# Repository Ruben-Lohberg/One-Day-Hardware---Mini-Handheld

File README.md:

# One-Day Hardware: Mini Handheld

**My goal was to design a handheld with a display and buttons in one day, including the PCB, enclosure, and firmware.**

I settled on a little handheld that plays Snake. By the end of the day, I'd routed the board, designed the case, and run the firmware in an emulator. I'd also ordered assembled boards from JLCPCB and parts from other vendors, and started printing the case and a PCB fit model.

## Tools

- KiCad 10.0 with the [JLCPCB Tools plugin](https://github.com/Bouni/kicad-jlcpcb-tools)
- FreeCAD 1.1.3
- Bambu Lab A1 3D printer and Bambu Studio
- Codex GPT-6.1 sol

## Try it while the boards are in the mail

**[Play Snake in your browser](https://ruben-lohberg.github.io/One-Day-Hardware---Mini-Handheld/)**. Press an arrow key or tap the on-screen D-pad to start. The demo runs the same Snake code compiled to WebAssembly and models how the TFT receives pixels over SPI.

Renode is an emulator that runs the compiled STM32 firmware on a virtual version of the handheld, with simulated buttons and a display.

To try it, run this from the repo on Windows with Python 3, LLVM, and Renode installed.

```powershell
.\firmware\run-web.ps1
```

Open [localhost:8765](http://127.0.0.1:8765/). The browser sends button presses to Renode and shows the pixels written by the STM32 firmware. The [firmware guide](firmware/README.md) has the commands for running the timing mock locally and testing the firmware.

## 1. Major component decisions

I knew I wanted JLCPCB to assemble the boards so I wouldn't have to solder all the small parts by hand. I compared microcontroller prices on JLCPCB and display prices on LCSC to find an affordable pair with enough memory for the game and a screen I could drive over SPI. Codex GPT-6.1 sol helped me compare the parts and check the pinouts and flex drawings.

- **STM32G070CBT6.** This is a 48-pin Arm Cortex-M0+ with up to 64 MHz clock speed, 128 KB of flash and 36 KB of RAM. It had enough memory for Snake and enough pins for the buttons, LEDs, SPI display and SWD. JLCPCB could fit it as part of the assembly order. [ST specifications](https://www.st.com/en/microcontrollers-microprocessors/stm32g070cb.html) · [JLCPCB C529338](https://jlcpcb.com/partdetail/STM32G070CBT6/C529338)
- **HS20HS072RX.** This is a 240 × 320 color TFT with a roughly 2-inch diagonal, an ST7789-family controller, a four-wire SPI interface and a 12-pin flex. It was small enough for the handheld and let me send pixel updates straight to the display without keeping a full screen buffer in the STM32's RAM. I could order the display separately and have JLCPCB fit the flex socket. [LCSC C5329582](https://www.lcsc.com/product-detail/C5329582.html) · [Display datasheet](https://datasheet.lcsc.com/datasheet/pdf/75d064ee0eeae326e605dda9d4b98e7e.pdf?productCode=C5329582)

## 2. KiCad schematic

I used USB-C for 5 V power and left the USB data lines unused. I brought out target voltage sense, ground, SWDIO, SWCLK, and reset to a five-pin header for the J-Link. With the STM32G070, four switches with pull-ups, and two red LEDs, I had something simple to test before asking the screen to do anything.

I used SPI for pixels, a GPIO for data/command and a PWM output for the backlight. I changed the logic rail from 3.3 V to 3.0 V to give the display supply more headroom and left the backlight on the USB rail. Codex GPT-6.1 sol helped cross-check the symbol pins and footprints against the drawings and run KiCad's electrical rule check.

Open the [KiCad project](mini_handheld/mini_handheld.kicad_pro) to see the schematic and board. The [assembly notes](manufacturing/jlcpcb/#swd-header) show how to wire the J-Link.

## 3. KiCad board

I chose surface-mount parts wherever I could and kept them on one side so JLCPCB could populate them in a single SMT assembly pass. That kept assembly costs down and left me two connectors to solder by hand. The right-angle SWD header is the through-hole exception, and the USB-C receptacle has surface-mount contacts and through-hole shell anchors.

My first outline was 60 × 95 mm. The display didn't need a board behind all of it, so I let the case carry the glass. That took the PCB down to **42 × 56 mm**. The display flex folds back under the panel into a bottom-contact socket. USB comes out on the left, SWD on the right, and the buttons stay in a cross below the display.

Both views use the same orientation so I can follow a trace through a via from one layer to the other. I hid the ground pours and silkscreen here to make the traces easier to follow.

On this board, the shortest trace wasn't always the one I wanted. I kept the display clock short while routing more of it over ground on the opposite layer. I also increased the spacing between the long SWD traces. Codex GPT-6.1 sol helped compare route lengths and ground coverage. KiCad found **zero ERC violations, zero board DRC violations, and zero unrouted connections**. The schematic parity check flagged the four mounting holes, which exist only on the PCB.

## 4. Electrical simulations

I wanted to see what the rail would do if USB sagged at the same time the load stepped up. With the USB source at 4.4 V and a simulated 25 → 75 mA load step, the 3.0 V rail dropped to **2.979 V** in the nominal case and **2.929 V** in the stress case. The deeper dip farther right is a separate input fault I added on purpose.

Codex GPT-6.1 sol helped write the SPICE decks and compare display clock edges using ST's IBIS output models. I chose medium GPIO slew and 2 MHz SPI for the first firmware. I'll measure the rail voltage and SPI clock with the real screen connected. See the [simulation files and commands](sim/README.md).

## 5. Emulation and firmware development

I started with the four buttons and two LEDs, then added a display diagnostic before moving on to Snake. Renode runs the compiled Cortex-M0+ firmware, and the virtual display turns its SPI writes into RGB565 pixels. The on-screen D-pad drives the same active-low GPIO inputs as the physical switches.

I added an animated rainbow border to show the display's color range and make refresh speed easier to see. The firmware cycles through RGB565 colors and aims to redraw the border about 30 times a second over the 2 MHz SPI link.

Codex GPT-6.1 sol helped with the STM32 code, Renode's SPI and display models, and the test scripts. The tests cover the buttons and LEDs, display updates, steering, growth, scoring, wall collisions and retry. I also checked that the model catches an early chip-select release and a missing PB15 setup bit. The [firmware notes](firmware/README.md) show how to run the checks.

## 6. FreeCAD enclosure

I exported the PCB from KiCad as a STEP file to check the fit in FreeCAD. The case supports the display on ledges and holds the PCB on four standoffs. I needed the flex to reach the socket without getting pinched by the lid.

Here's the full board with the display in place. The inset shows how the orange flex folds back under the panel and enters the Hirose socket. I made the socket translucent in FreeCAD so you can see where the end of the flex sits.

The case measures **47.2 × 95.2 × 15.0 mm**, excluding the buttons. It has a tray, a bezel, and four individual plungers. A lip on each plunger keeps it in the bezel while the case is closed. Codex GPT-6.1 sol helped me script the geometry and check the clearances with the buttons released and pressed.

The [FreeCAD model](mechanical/enclosure/enclosure.FCStd), [assembly notes and STLs](mechanical/enclosure/README.md) and [STEP export workflow](mechanical/README.md) are in the repo.

## 7. Order board and parts

I ordered five boards from JLCPCB with the surface-mount parts and flex socket fitted. I'll solder the USB-C receptacle and SWD header myself, then plug in the separately ordered display. Codex GPT-6.1 sol helped compare assembly costs and check the placement file. The [manufacturing folder](manufacturing/jlcpcb/) has the upload files and a short parts list.

## 8. 3D print prototype

I started printing the enclosure and a PCB fit model while waiting for the parts. The fit model gives me the board outline, mounting holes and connector envelopes so I can check the tray and ports without risking a real board.

This is the saved slicer preview of the fit-print arrangement. Use the [current STLs](mechanical/enclosure/README.md) when preparing a new print.

I printed the tray, bezel, four button plungers, and stand-ins for the PCB and screen.

I dropped the printed PCB and screen into the tray. With the bezel beside it, I can see where the board sits and how the screen lines up with the window.

Here it is with the bezel on and all four buttons in place. From the side you can see where the connector opening lands.

Once the parts are here, I'll add photos of the delivered boards and first assembly. On the bench I'll check for shorts, measure the 3.0 V rail, connect J-Link and run the button/LED and screen diagnostics before trying Snake. I still need to check the flex latch, USB plug clearance and switch travel on real parts.

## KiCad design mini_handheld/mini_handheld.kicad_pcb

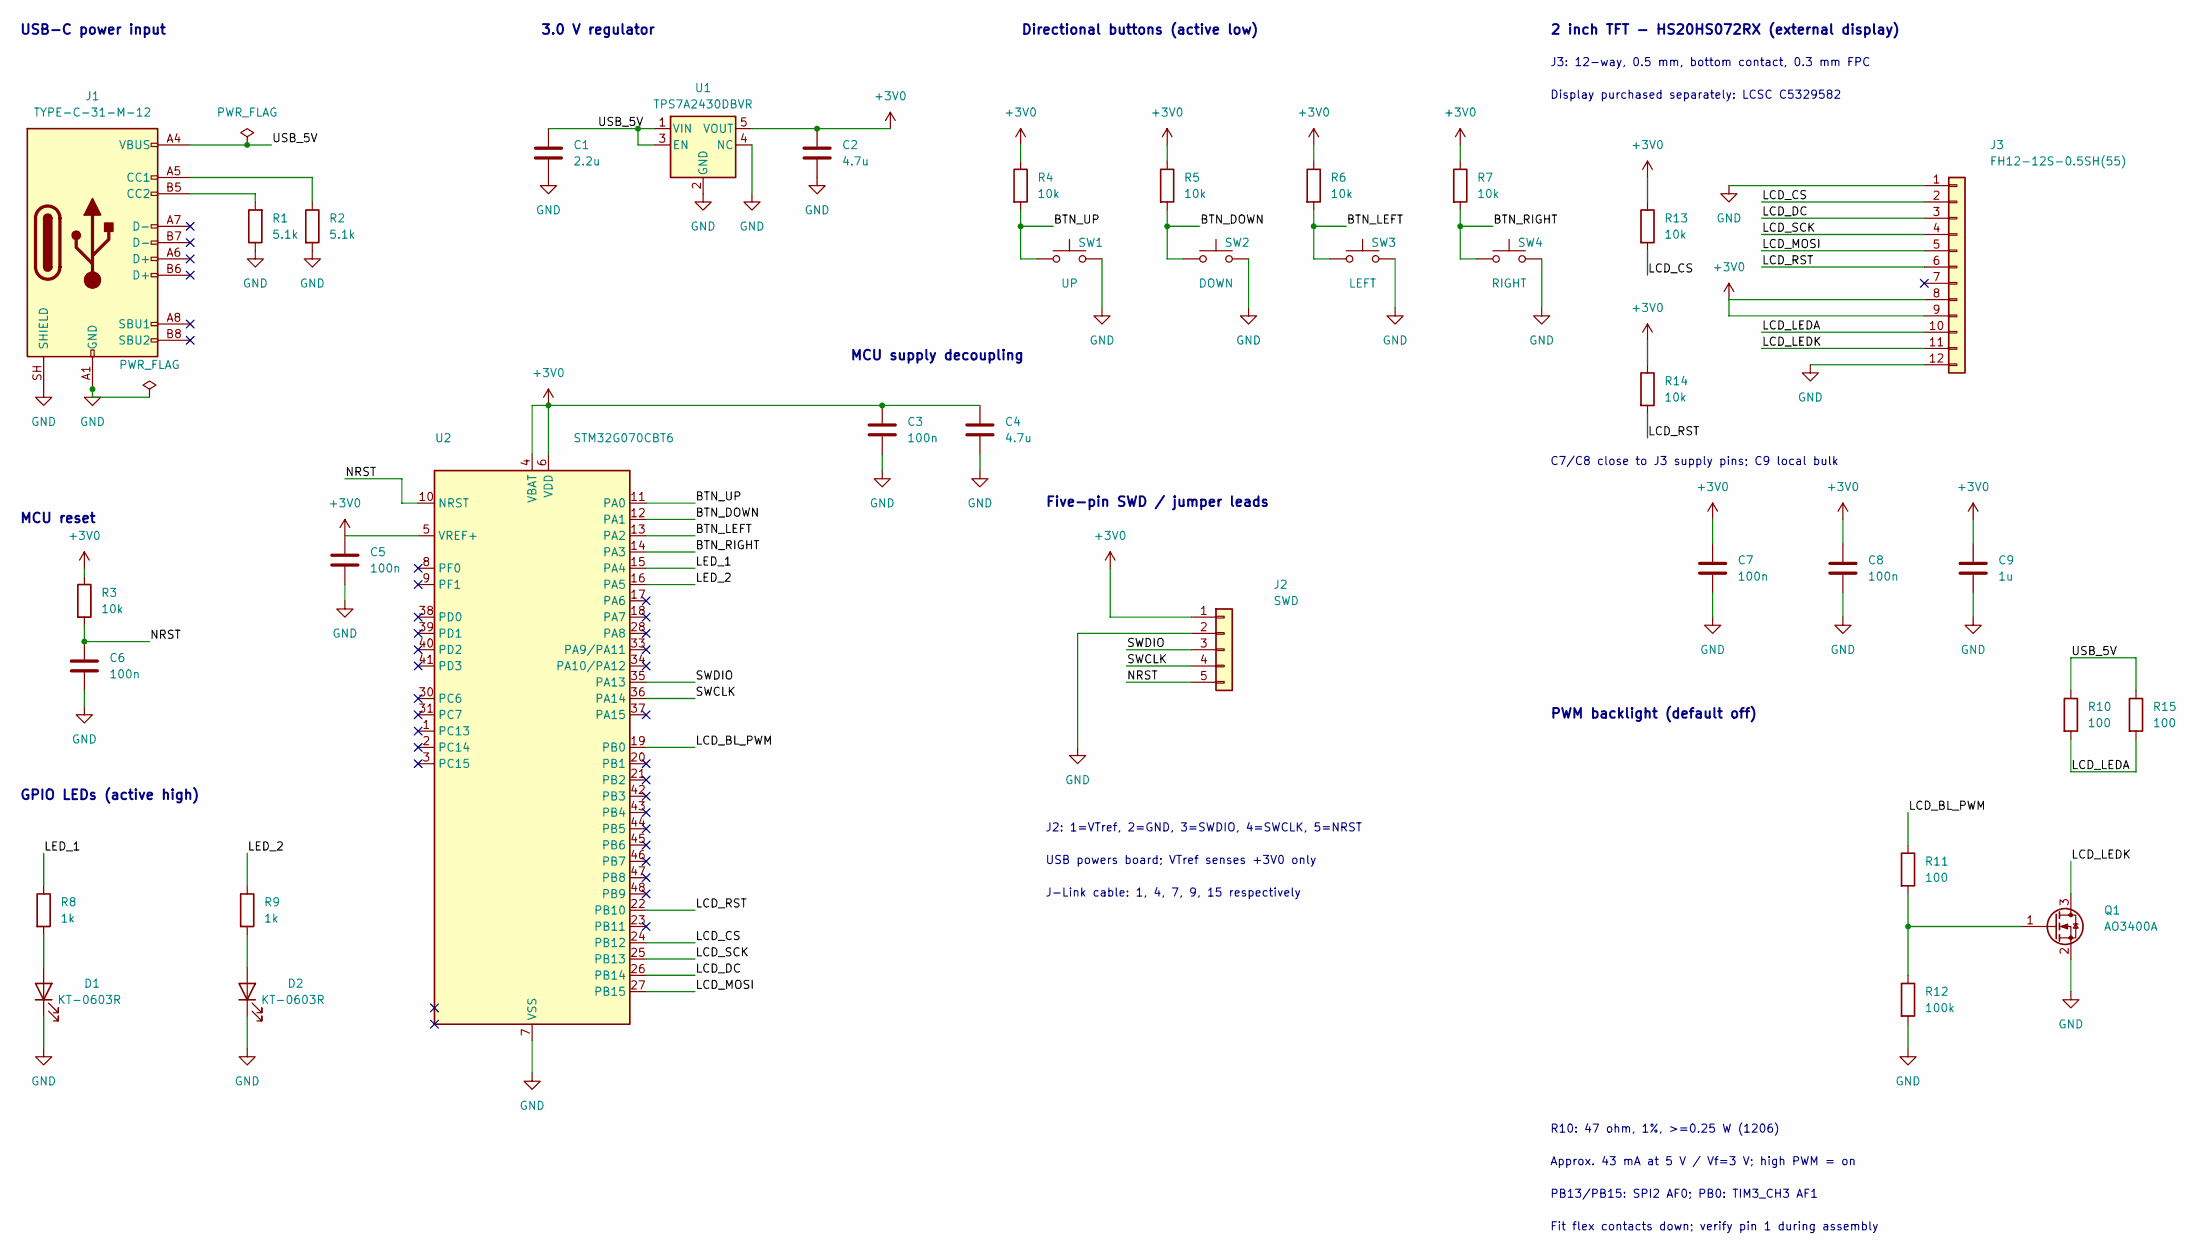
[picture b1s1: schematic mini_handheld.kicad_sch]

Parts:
C1: 2.2u; C_0603_1608Metric; Tolerance 10%; Voltage 50V; MPN CL10A225KO8NNNC; LCSC C23630
C2, C4: 4.7u; C_0805_2012Metric; Tolerance 10%; Voltage 25V; MPN CL21A475KAQNNNE; LCSC C1779
C3, C5, C6, C7, C8: 100n; C_0603_1608Metric; Tolerance 10%; Voltage 50V; MPN CC0603KRX7R9BB104; LCSC C14663
C9: 1u; C_0603_1608Metric; Tolerance 10%; Voltage 50V; MPN CL10A105KB8NNNC; LCSC C15849
D1, D2: KT-0603R; LED_0603_1608Metric; MPN KT-0603R; LCSC C2286
J1: TYPE-C-31-M-12; USB_C_Receptacle_HRO_TYPE-C-31-M-12_Edge; MPN TYPE-C-31-M-12; LCSC C165948
J2: SWD; PinHeader_1x05_P2.54mm_Horizontal_Edge
J3: FH12-12S-0.5SH(55); Hirose_FH12-12S-0.5SH_1x12-1MP_P0.50mm_Horizontal; MPN FH12-12S-0.5SH(55); LCSC C88360
Q1: AO3400A; SOT-23; MPN AO3400A; LCSC C20917
R1, R2: 5.1k; R_0603_1608Metric; Tolerance 1%; Voltage 75V; MPN 0603WAF5101T5E; LCSC C23186
R3, R4, R5, R6, R7, R13, R14: 10k; R_0603_1608Metric; Tolerance 1%; Voltage 75V; MPN 0603WAF1002T5E; LCSC C25804
R8, R9: 1k; R_0603_1608Metric; Tolerance 1%; Voltage 75V; MPN 0603WAF1001T5E; LCSC C21190
R10, R11, R15: 100; R_0603_1608Metric; Tolerance 1%; Voltage 75V; MPN 0603WAF1000T5E; LCSC C22775
R12: 100k; R_0603_1608Metric; Tolerance 1%; Voltage 75V; MPN 0603WAF1003T5E; LCSC C25803
SW1: UP; SW_SPST_TS-1088-xR020; MPN TS-1088-AR02016; LCSC C720477
SW2: DOWN; SW_SPST_TS-1088-xR020; MPN TS-1088-AR02016; LCSC C720477
SW3: LEFT; SW_SPST_TS-1088-xR020; MPN TS-1088-AR02016; LCSC C720477
SW4: RIGHT; SW_SPST_TS-1088-xR020; MPN TS-1088-AR02016; LCSC C720477
U1: TPS7A2430DBVR; SOT-23-5; MPN TPS7A2430DBVR; LCSC C2864435
U2: STM32G070CBT6; LQFP-48_7x7mm_P0.5mm; MPN STM32G070CBT6; LCSC C529338

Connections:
+3V0: C2.1, C3.1, C4.1, C5.1, C7.1, C8.1, C9.1, J2.1, J3.8, J3.9, R3.1, R4.1, R5.1, R6.1, R7.1, R13.1, R14.1, U1.5 (VOUT), U2.4 (VBAT), U2.5 (VREF+), U2.6 (VDD)
/BTN_DOWN: R5.2, SW2.1, U2.12 (PA1)
/BTN_LEFT: R6.2, SW3.1, U2.13 (PA2)
/BTN_RIGHT: R7.2, SW4.1, U2.14 (PA3)
/BTN_UP: R4.2, SW1.1, U2.11 (PA0)
/LCD_BL_PWM: R11.1, U2.19 (PB0)
/LCD_CS: J3.2, R13.2, U2.24 (PB12)
/LCD_DC: J3.3, U2.26 (PB14)
/LCD_LEDA: J3.10, R10.2, R15.2
/LCD_LEDK: J3.11, Q1.3 (D)
/LCD_MOSI: J3.5, U2.27 (PB15)
/LCD_RST: J3.6, R14.2, U2.22 (PB10)
/LCD_SCK: J3.4, U2.25 (PB13)
/LED_1: R8.1, U2.15 (PA4)
/LED_2: R9.1, U2.16 (PA5)
/NRST: C6.1, J2.5, R3.2, U2.10 (NRST)
/SWCLK: J2.4, U2.36 (PA14)
/SWDIO: J2.3, U2.35 (PA13)
/USB_5V: C1.1, J1.A4 (VBUS), J1.A9 (VBUS), J1.B4 (VBUS), J1.B9 (VBUS), R10.1, R15.1, U1.1 (VIN), U1.3 (EN)
GND: C1.2, C2.2, C3.2, C4.2, C5.2, C6.2, C7.2, C8.2, C9.2, D1.1 (K), D2.1 (K), J1.A1 (GND), J1.A12 (GND), J1.B1 (GND), J1.B12 (GND), J1.SH (SHIELD), J2.2, J3.1, J3.12, Q1.2 (S), R1.1, R2.2, R12.2, SW1.2, SW2.2, SW3.2, SW4.2, U1.2 (GND), U1.4 (NC), U2.7 (VSS)
unnamed: D1.2 (A), R8.2
unnamed: D2.2 (A), R9.2
unnamed: J1.A5 (CC1), R2.1
unnamed: J1.B5 (CC2), R1.2
unnamed: Q1.1 (G), R11.2, R12.1

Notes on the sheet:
3.0 V regulator
Fit flex contacts down; verify pin 1 during assembly
GPIO LEDs (active high)
J2: 1=VTref, 2=GND, 3=SWDIO, 4=SWCLK, 5=NRST
Display purchased separately: LCSC C5329582
PWM backlight (default off)
MCU reset
MCU supply decoupling
J-Link cable: 1, 4, 7, 9, 15 respectively
Approx. 43 mA at 5 V / Vf=3 V; high PWM = on
PB13/PB15: SPI2 AF0; PB0: TIM3_CH3 AF1
Five-pin SWD / jumper leads
J3: 12-way, 0.5 mm, bottom contact, 0.3 mm FPC
USB-C power input
2 inch TFT - HS20HS072RX (external display)
Directional buttons (active low)
C7/C8 close to J3 supply pins; C9 local bulk
R10: 47 ohm, 1%, >=0.25 W (1206)
USB powers board; VTref senses +3V0 only

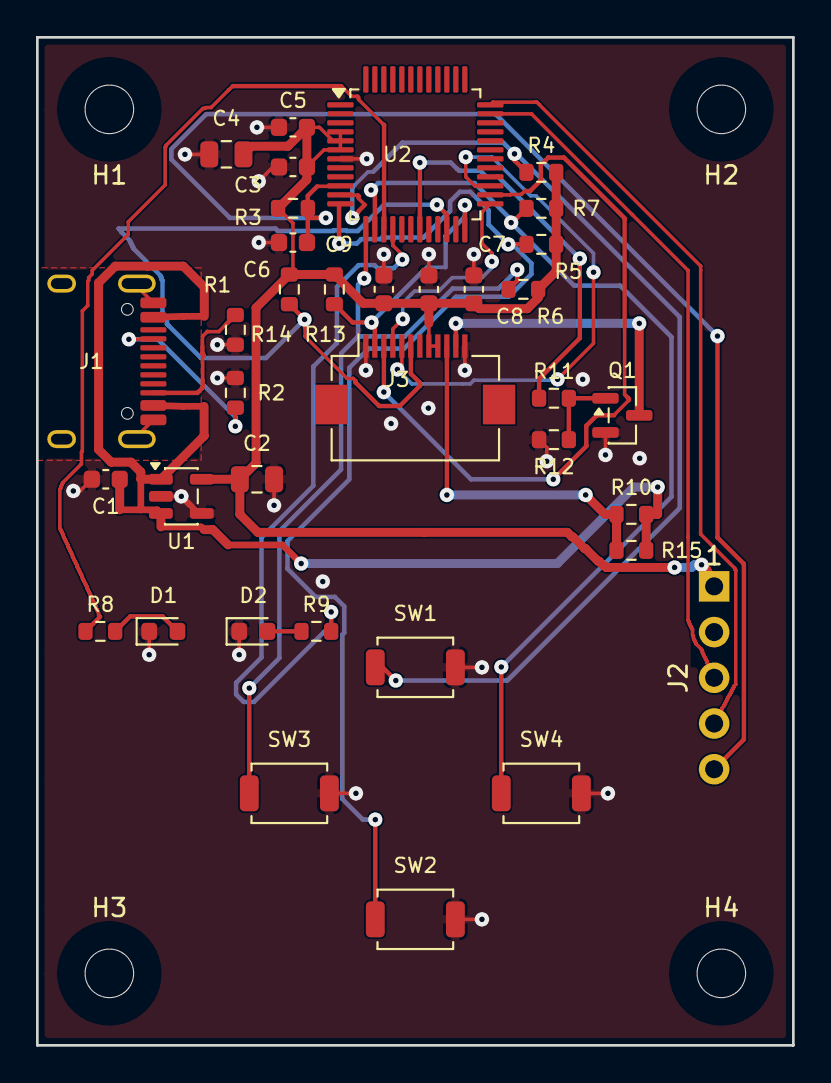
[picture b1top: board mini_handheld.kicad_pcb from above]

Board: 2 copper layers, 42.0 x 56.0 mm, 40 parts (0 on the bottom side), 25 nets.

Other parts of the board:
H1, H2, H3, H4: MountingHole_2.7mm_M2.5

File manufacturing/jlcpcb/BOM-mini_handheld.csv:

Comment,Designator,Footprint,LCSC,Quantity
100,"R10,R11,R15",R_0603_1608Metric,C22775,3
100k,R12,R_0603_1608Metric,C25803,1
100n,"C3,C5,C6,C7,C8",C_0603_1608Metric,C14663,5
10k,"R13,R14,R3,R4,R5,R6,R7",R_0603_1608Metric,C25804,7
1k,"R8,R9",R_0603_1608Metric,C21190,2
1u,C9,C_0603_1608Metric,C15849,1
2.2u,C1,C_0603_1608Metric,C23630,1
4.7u,"C2,C4",C_0805_2012Metric,C1779,2
5.1k,"R1,R2",R_0603_1608Metric,C23186,2
AO3400A,Q1,SOT-23,C20917,1
FH12-12S-0.5SH(55),J3,Hirose_FH12-12S-0.5SH_1x12-1MP_P0.50mm_Horizontal,C88360,1
KT-0603R,"D1,D2",LED_0603_1608Metric,C2286,2
STM32G070CBT6,U2,LQFP-48_7x7mm_P0.5mm,C529338,1
TPS7A2430DBVR,U1,SOT-23-5,C2864435,1
TS-1088-AR02016,"SW1,SW2,SW3,SW4",SW_SPST_TS-1088-xR020,C720477,4

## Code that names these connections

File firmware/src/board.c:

#include "board.h"

// STM32G070 GPIO register layout (RM0454).
#define REG32(addr) (*(volatile uint32_t *)(addr))
#define RCC_IOPENR  REG32(0x40021034u)
#define GPIOA_MODER REG32(0x50000000u)
#define GPIOA_OTYPER REG32(0x50000004u)
#define GPIOA_PUPDR REG32(0x5000000cu)
#define GPIOA_IDR   REG32(0x50000010u)
#define GPIOA_BSRR  REG32(0x50000018u)

enum {
    BUTTON_PINS = 0x0fu,   // PA0–PA3, external pull-ups
    LED1_PIN = 1u << 4,
    LED2_PIN = 1u << 5,
    LED_PINS = LED1_PIN | LED2_PIN,
};

void board_init(void)
{
    RCC_IOPENR |= 1u;      // GPIOA clock
    (void)RCC_IOPENR;     // Allow clock enable to take effect
    GPIOA_BSRR = LED_PINS << 16;
    GPIOA_OTYPER &= ~(uint32_t)LED_PINS;
    GPIOA_PUPDR &= ~0xfffu;
    // Only change PA0–PA5. Leave PA13/PA14 configured for SWD.
    GPIOA_MODER = (GPIOA_MODER & ~0xfffu) | (1u << 8) | (1u << 10);
}

uint32_t board_buttons(void)
{
    return ~GPIOA_IDR & BUTTON_PINS;
}

void board_leds(bool led1, bool led2)
{
    const uint32_t on = (led1 ? LED1_PIN : 0u) | (led2 ? LED2_PIN : 0u);
    GPIOA_BSRR = on | ((LED_PINS & ~on) << 16);
}
